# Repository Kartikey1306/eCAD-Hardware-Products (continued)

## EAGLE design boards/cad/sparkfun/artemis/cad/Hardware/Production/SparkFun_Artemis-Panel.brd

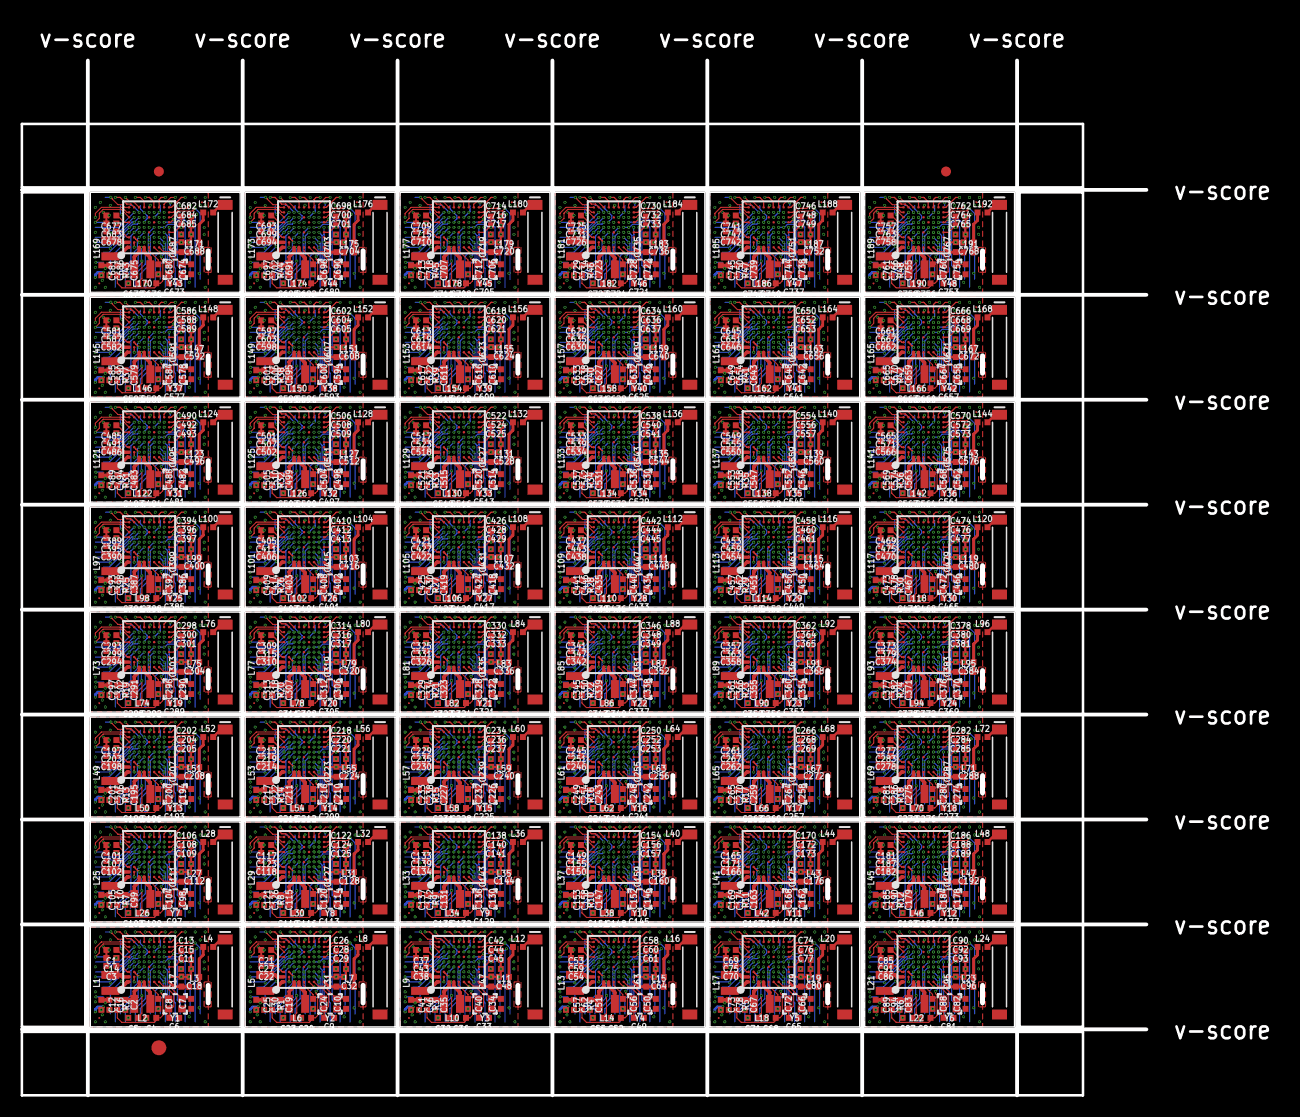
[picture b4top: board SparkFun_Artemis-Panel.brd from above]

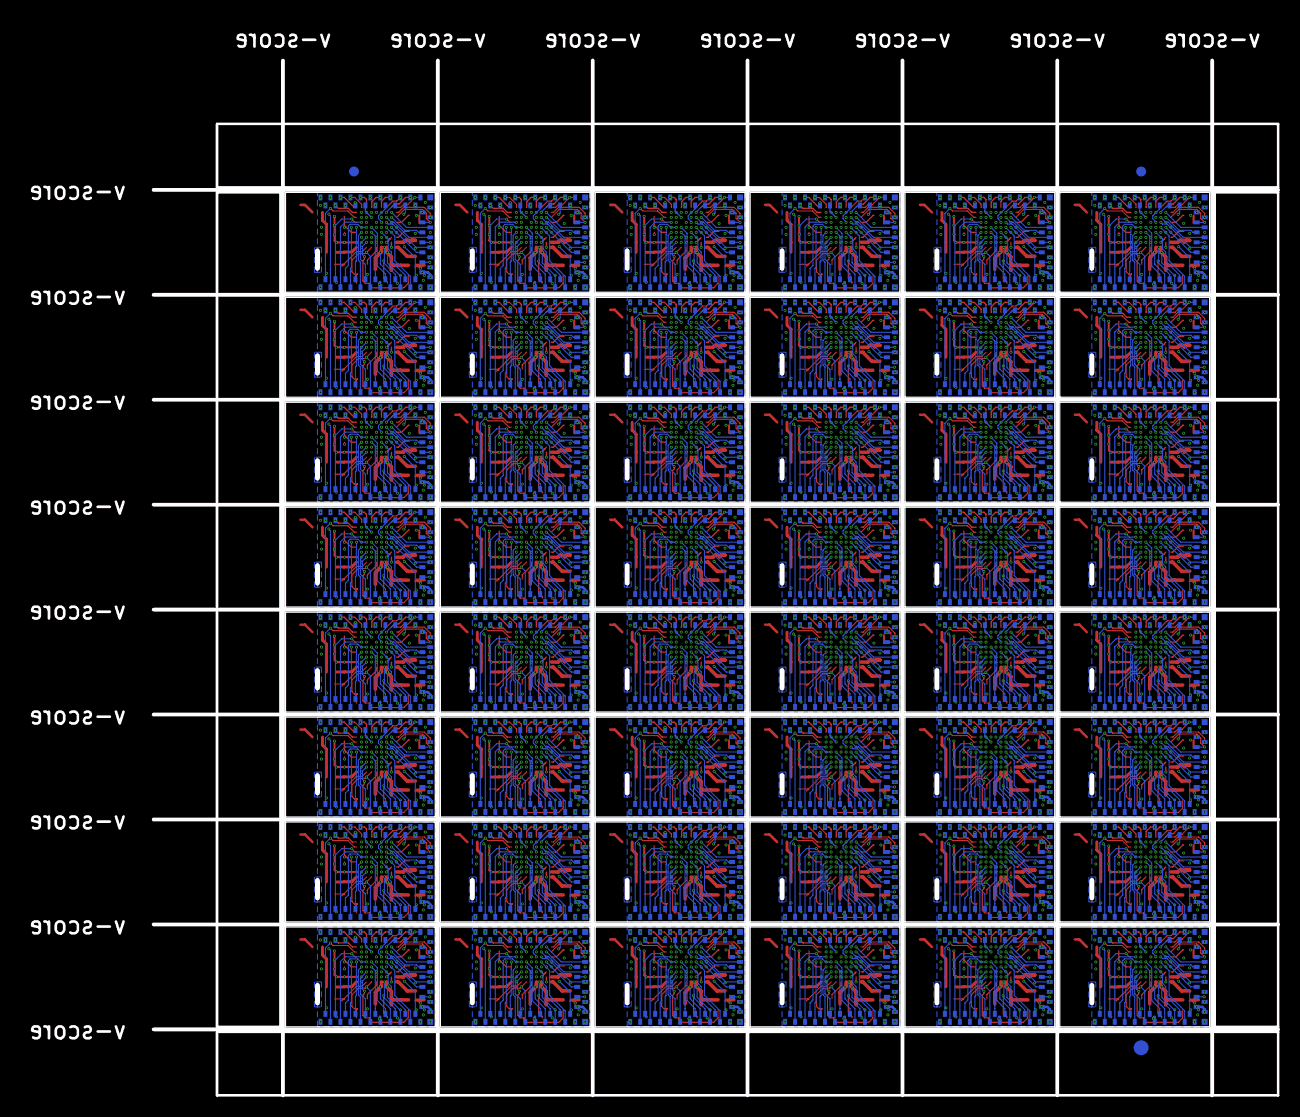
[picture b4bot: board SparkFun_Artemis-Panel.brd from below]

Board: 4 copper layers, 112.6 x 103.6 mm, 4134 parts (2835 on the bottom side), 3264 nets.

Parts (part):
A1, A2, A3, A4, A5, A6, A7, A8, A9, A10, A11, A12, A13, A14, A15, A16, A17, A18, A19, A20, A21, A22, A23, A24, A25, A26, A27, A28, A29, A30, A31, A32, A33, A34, A35, A36, A37, A38, A39, A40, A41, A42, A43, A44, A45, A46, A47, A48: 2.4GHZ-3.2X1.6MM; ANT-2.4GHZ-8.0X1.0MM
C1, C21, C37, C53, C69, C85, C101, C117, C133, C149, C165, C181, C197, C213, C229, C245, C261, C277, C293, C309, C325, C341, C357, C373, C389, C405, C421, C437, C453, C469, C485, C501, C517, C533, C549, C565, C581, C597, C613, C629, C645, C661, C677, C693, C709, C725, C741, C757: 0.47uF; 0402-TIGHT
C2, C19, C35, C51, C67, C83, C99, C115, C131, C147, C163, C179, C195, C211, C227, C243, C259, C275, C291, C307, C323, C339, C355, C371, C387, C403, C419, C435, C451, C467, C483, C499, C515, C531, C547, C563, C579, C595, C611, C627, C643, C659, C675, C691, C707, C723, C739, C755: 4.7uF; 0402-TIGHT
C3, C5, C8, C16, C22, C23, C24, C30, C38, C39, C40, C46, C54, C55, C56, C62, C70, C71, C72, C78, C86, C87, C88, C94, C102, C103, C104, C110, C118, C119, C120, C126, C134, C135, C136, C142, C150, C151, C152, C158, C166, C167, C168, C174, C182, C183, C184, C190, C198, C199, C200, C206, C214, C215, C216, C222, C230, C231, C232, C238, C246, C247, C248, C254, C262, C263, C264, C270, C278, C279, C280, C286, C294, C295, C296, C302, C310, C311, C312, C318, C326, C327, C328, C334, C342, C343, C344, C350, C358, C359, C360, C366, C374, C375, C376, C382, C390, C391, C392, C398, C406, C407, C408, C414, C422, C423, C424, C430, C438, C439, C440, C446, C454, C455, C456, C462, C470, C471, C472, C478, C486, C487, C488, C494, C502, C503, C504, C510, C518, C519, C520, C526, C534, C535, C536, C542, C550, C551, C552, C558, C566, C567, C568, C574, C582, C583, C584, C590, C598, C599, C600, C606, C614, C615, C616, C622, C630, C631, C632, C638, C646, C647, C648, C654, C662, C663, C664, C670, C678, C679, C680, C686, C694, C695, C696, C702, C710, C711, C712, C718, C726, C727, C728, C734, C742, C743, C744, C750, C758, C759, C760, C766: 2.2uF; 0402-TIGHT
C4, C12, C13, C14, C15, C20, C25, C26, C27, C28, C36, C41, C42, C43, C44, C52, C57, C58, C59, C60, C68, C73, C74, C75, C76, C84, C89, C90, C91, C92, C100, C105, C106, C107, C108, C116, C121, C122, C123, C124, C132, C137, C138, C139, C140, C148, C153, C154, C155, C156, C164, C169, C170, C171, C172, C180, C185, C186, C187, C188, C196, C201, C202, C203, C204, C212, C217, C218, C219, C220, C228, C233, C234, C235, C236, C244, C249, C250, C251, C252, C260, C265, C266, C267, C268, C276, C281, C282, C283, C284, C292, C297, C298, C299, C300, C308, C313, C314, C315, C316, C324, C329, C330, C331, C332, C340, C345, C346, C347, C348, C356, C361, C362, C363, C364, C372, C377, C378, C379, C380, C388, C393, C394, C395, C396, C404, C409, C410, C411, C412, C420, C425, C426, C427, C428, C436, C441, C442, C443, C444, C452, C457, C458, C459, C460, C468, C473, C474, C475, C476, C484, C489, C490, C491, C492, C500, C505, C506, C507, C508, C516, C521, C522, C523, C524, C532, C537, C538, C539, C540, C548, C553, C554, C555, C556, C564, C569, C570, C571, C572, C580, C585, C586, C587, C588, C596, C601, C602, C603, C604, C612, C617, C618, C619, C620, C628, C633, C634, C635, C636, C644, C649, C650, C651, C652, C660, C665, C666, C667, C668, C676, C681, C682, C683, C684, C692, C697, C698, C699, C700, C708, C713, C714, C715, C716, C724, C729, C730, C731, C732, C740, C745, C746, C747, C748, C756, C761, C762, C763, C764: 1.0uF; 0402-TIGHT
C6, C7, C9, C10, C33, C34, C49, C50, C65, C66, C81, C82, C97, C98, C113, C114, C129, C130, C145, C146, C161, C162, C177, C178, C193, C194, C209, C210, C225, C226, C241, C242, C257, C258, C273, C274, C289, C290, C305, C306, C321, C322, C337, C338, C353, C354, C369, C370, C385, C386, C401, C402, C417, C418, C433, C434, C449, C450, C465, C466, C481, C482, C497, C498, C513, C514, C529, C530, C545, C546, C561, C562, C577, C578, C593, C594, C609, C610, C625, C626, C641, C642, C657, C658, C673, C674, C689, C690, C705, C706, C721, C722, C737, C738, C753, C754: 6pF; 0402-TIGHT
C11, C29, C45, C61, C77, C93, C109, C125, C141, C157, C173, C189, C205, C221, C237, C253, C269, C285, C301, C317, C333, C349, C365, C381, C397, C413, C429, C445, C461, C477, C493, C509, C525, C541, C557, C573, C589, C605, C621, C637, C653, C669, C685, C701, C717, C733, C749, C765: 47nF; 0402-TIGHT
C17, C31, C47, C63, C79, C95, C111, C127, C143, C159, C175, C191, C207, C223, C239, C255, C271, C287, C303, C319, C335, C351, C367, C383, C399, C415, C431, C447, C463, C479, C495, C511, C527, C543, C559, C575, C591, C607, C623, C639, C655, C671, C687, C703, C719, C735, C751, C767: DNP; 0402-TIGHT
C18, C32, C48, C64, C80, C96, C112, C128, C144, C160, C176, C192, C208, C224, C240, C256, C272, C288, C304, C320, C336, C352, C368, C384, C400, C416, C432, C448, C464, C480, C496, C512, C528, C544, C560, C576, C592, C608, C624, C640, C656, C672, C688, C704, C720, C736, C752, C768: 0.5pF; 0402-TIGHT
E$1, E$2, E$3, E$4: FIDUCIAL-1X2
E$5, E$6: FIDUCIAL-1.5X3
FD1, FD2, FD3, FD4, FD5, FD6, FD7, FD8, FD9, FD10, FD11, FD12, FD13, FD14, FD15, FD16, FD17, FD18, FD19, FD20, FD21, FD22, FD23, FD24, FD25, FD26, FD27, FD28, FD29, FD30, FD31, FD32, FD33, FD34, FD35, FD36, FD37, FD38, FD39, FD40, FD41, FD42, FD43, FD44, FD45, FD46, FD47, FD48, FD49, FD50, FD51, FD52, FD53, FD54, FD55, FD56, FD57, FD58, FD59, FD60, FD61, FD62, FD63, FD64, FD65, FD66, FD67, FD68, FD69, FD70, FD71, FD72, FD73, FD74, FD75, FD76, FD77, FD78, FD79, FD80, FD81, FD82, FD83, FD84, FD85, FD86, FD87, FD88, FD89, FD90, FD91, FD92, FD93, FD94, FD95, FD96: FIDUCIAL0.2MM; FIDUCIAL-0.2MM
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
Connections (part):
!RST: J50.1, U1.G3
!RST1: J83.1, U2.G3
!RST2: J142.1, U3.G3
!RST3: J201.1, U4.G3
!RST4: J260.1, U5.G3
!RST5: J319.1, U6.G3
!RST6: J378.1, U7.G3
!RST7: J437.1, U8.G3
!RST8: J496.1, U9.G3
!RST9: J555.1, U10.G3
!RST10: J614.1, U11.G3
!RST11: J673.1, U12.G3
!RST12: J732.1, U13.G3
!RST13: J791.1, U14.G3
!RST14: J850.1, U15.G3
!RST15: J909.1, U16.G3
!RST16: J968.1, U17.G3
!RST17: J1027.1, U18.G3
!RST18: J1086.1, U19.G3
!RST19: J1145.1, U20.G3
!RST20: J1204.1, U21.G3
!RST21: J1263.1, U22.G3
!RST22: J1322.1, U23.G3
!RST23: J1381.1, U24.G3
!RST24: J1440.1, U25.G3
!RST25: J1499.1, U26.G3
!RST26: J1558.1, U27.G3
!RST27: J1617.1, U28.G3
!RST28: J1676.1, U29.G3
!RST29: J1735.1, U30.G3
!RST30: J1794.1, U31.G3
!RST31: J1853.1, U32.G3
!RST32: J1912.1, U33.G3
!RST33: J1971.1, U34.G3
!RST34: J2030.1, U35.G3
!RST35: J2089.1, U36.G3
!RST36: J2148.1, U37.G3
!RST37: J2207.1, U38.G3
!RST38: J2266.1, U39.G3
!RST39: J2325.1, U40.G3
!RST40: J2384.1, U41.G3
!RST41: J2443.1, U42.G3
!RST42: J2502.1, U43.G3
!RST43: J2561.1, U44.G3
!RST44: J2620.1, U45.G3
!RST45: J2679.1, U46.G3
!RST46: J2738.1, U47.G3
!RST47: J2797.1, U48.G3
ADC_VREF: C1.1, U1.A6
ADC_VREF1: C21.1, U2.A6
ADC_VREF2: C37.1, U3.A6
ADC_VREF3: C53.1, U4.A6
ADC_VREF4: C69.1, U5.A6
ADC_VREF5: C85.1, U6.A6
ADC_VREF6: C101.1, U7.A6
ADC_VREF7: C117.1, U8.A6
ADC_VREF8: C133.1, U9.A6
ADC_VREF9: C149.1, U10.A6
ADC_VREF10: C165.1, U11.A6
ADC_VREF11: C181.1, U12.A6
ADC_VREF12: C197.1, U13.A6
ADC_VREF13: C213.1, U14.A6
ADC_VREF14: C229.1, U15.A6
ADC_VREF15: C245.1, U16.A6
ADC_VREF16: C261.1, U17.A6
ADC_VREF17: C277.1, U18.A6
ADC_VREF18: C293.1, U19.A6
ADC_VREF19: C309.1, U20.A6
ADC_VREF20: C325.1, U21.A6
ADC_VREF21: C341.1, U22.A6
ADC_VREF22: C357.1, U23.A6
ADC_VREF23: C373.1, U24.A6
ADC_VREF24: C389.1, U25.A6
ADC_VREF25: C405.1, U26.A6
ADC_VREF26: C421.1, U27.A6
ADC_VREF27: C437.1, U28.A6
ADC_VREF28: C453.1, U29.A6
ADC_VREF29: C469.1, U30.A6
ADC_VREF30: C485.1, U31.A6
ADC_VREF31: C501.1, U32.A6
ADC_VREF32: C517.1, U33.A6
ADC_VREF33: C533.1, U34.A6
ADC_VREF34: C549.1, U35.A6
ADC_VREF35: C565.1, U36.A6
ADC_VREF36: C581.1, U37.A6
ADC_VREF37: C597.1, U38.A6
ADC_VREF38: C613.1, U39.A6
ADC_VREF39: C629.1, U40.A6
ADC_VREF40: C645.1, U41.A6
ADC_VREF41: C661.1, U42.A6
ADC_VREF42: C677.1, U43.A6
ADC_VREF43: C693.1, U44.A6
ADC_VREF44: C709.1, U45.A6
ADC_VREF45: C725.1, U46.A6
ADC_VREF46: C741.1, U47.A6
ADC_VREF47: C757.1, U48.A6
BOOTLOAD: J7.1, U1.H9
BOOTLOAD1: J62.1, U2.H9
BOOTLOAD2: J121.1, U3.H9
BOOTLOAD3: J180.1, U4.H9
BOOTLOAD4: J239.1, U5.H9
BOOTLOAD5: J298.1, U6.H9
BOOTLOAD6: J357.1, U7.H9
BOOTLOAD7: J416.1, U8.H9
BOOTLOAD8: J475.1, U9.H9
BOOTLOAD9: J534.1, U10.H9
BOOTLOAD10: J593.1, U11.H9
BOOTLOAD11: J652.1, U12.H9
BOOTLOAD12: J711.1, U13.H9
BOOTLOAD13: J770.1, U14.H9
BOOTLOAD14: J829.1, U15.H9
BOOTLOAD15: J888.1, U16.H9
BOOTLOAD16: J947.1, U17.H9
BOOTLOAD17: J1006.1, U18.H9
BOOTLOAD18: J1065.1, U19.H9
BOOTLOAD19: J1124.1, U20.H9
BOOTLOAD20: J1183.1, U21.H9
BOOTLOAD21: J1242.1, U22.H9
BOOTLOAD22: J1301.1, U23.H9
BOOTLOAD23: J1360.1, U24.H9
BOOTLOAD24: J1419.1, U25.H9
BOOTLOAD25: J1478.1, U26.H9
BOOTLOAD26: J1537.1, U27.H9
BOOTLOAD27: J1596.1, U28.H9
BOOTLOAD28: J1655.1, U29.H9
BOOTLOAD29: J1714.1, U30.H9
BOOTLOAD30: J1773.1, U31.H9
BOOTLOAD31: J1832.1, U32.H9
BOOTLOAD32: J1891.1, U33.H9
BOOTLOAD33: J1950.1, U34.H9
BOOTLOAD34: J2009.1, U35.H9
BOOTLOAD35: J2068.1, U36.H9
BOOTLOAD36: J2127.1, U37.H9
BOOTLOAD37: J2186.1, U38.H9
BOOTLOAD38: J2245.1, U39.H9
BOOTLOAD39: J2304.1, U40.H9
BOOTLOAD40: J2363.1, U41.H9
BOOTLOAD41: J2422.1, U42.H9
BOOTLOAD42: J2481.1, U43.H9
BOOTLOAD43: J2540.1, U44.H9
BOOTLOAD44: J2599.1, U45.H9
BOOTLOAD45: J2658.1, U46.H9
BOOTLOAD46: J2717.1, U47.H9
BOOTLOAD47: J2776.1, U48.H9
D0: J51.1, U1.H4
D1: J49.1, U1.G4
D2: J48.1, U1.F4
D3: J54.1, U1.G5
D4: J77.1, U2.F9
D5: J80.1, U2.J9
D6: J92.1, U2.J6
D7: J13.1, U1.F9
D8: J11.1, U1.F8
D9: J6.1, U1.G7
D10: J8.1, U1.G8
D11: J94.1, U2.H6
D12: J98.1, U2.F8
D13: J99.1, U2.G8
D14: J20.1, U1.D7
D15: J29.1, U1.C7
D16: J42.1, U1.D4
D17: J43.1, U1.D3
D18: J41.1, U1.C5
D19: J40.1, U1.C3
D20: J101.1, U2.G7
D21: J107.1, U2.G5
D22: J106.1, U2.F4
D23: J18.1, U1.D8
D24: J105.1, U2.G4
D25: J104.1, U2.H4
D26: J108.1, U2.D7
D27: J109.1, U2.C7
D28: J110.1, U2.D4
D29: J111.1, U2.D3
D30: J112.1, U2.C5
D31: J113.1, U2.C3
D32: J114.1, U2.D8
D33: J115.1, U2.C6
D34: J31.1, U1.C6
D35: J116.1, U2.E5
D36: J55.1, U1.H6
D37: J117.1, U2.F5
D38: J56.1, U1.J6
D39: J136.1, U3.F9
D40: J5.1, U1.J9
D41: J45.1, U1.E5
D42: J139.1, U3.J9
D43: J151.1, U3.J6
D44: J153.1, U3.H6
D45: J46.1, U1.F5
D46: J157.1, U3.F8
D47: J158.1, U3.G8
D48: J160.1, U3.G7
D49: J166.1, U3.G5
D50: J165.1, U3.F4
D51: J164.1, U3.G4
D52: J163.1, U3.H4
D53: J167.1, U3.D7
D54: J168.1, U3.C7
D55: J169.1, U3.D4
D56: J170.1, U3.D3
D57: J171.1, U3.C5
D58: J172.1, U3.C3
D59: J173.1, U3.D8
D60: J174.1, U3.C6
D61: J175.1, U3.E5
D62: J176.1, U3.F5
D63: J195.1, U4.F9
D64: J198.1, U4.J9
D65: J210.1, U4.J6
D66: J212.1, U4.H6
D67: J216.1, U4.F8
D68: J217.1, U4.G8
D69: J219.1, U4.G7
D70: J225.1, U4.G5
D71: J224.1, U4.F4
D72: J223.1, U4.G4
D73: J222.1, U4.H4
D74: J226.1, U4.D7
D75: J227.1, U4.C7
D76: J228.1, U4.D4
D77: J229.1, U4.D3
D78: J230.1, U4.C5
D79: J231.1, U4.C3
D80: J232.1, U4.D8
D81: J233.1, U4.C6
D82: J234.1, U4.E5
D83: J235.1, U4.F5
D84: J254.1, U5.F9
D85: J257.1, U5.J9
D86: J269.1, U5.J6
D87: J271.1, U5.H6
D88: J275.1, U5.F8
D89: J276.1, U5.G8
D90: J278.1, U5.G7
D91: J284.1, U5.G5
D92: J283.1, U5.F4
D93: J282.1, U5.G4
D94: J281.1, U5.H4
D95: J285.1, U5.D7
D96: J286.1, U5.C7
D97: J287.1, U5.D4
D98: J288.1, U5.D3
D99: J289.1, U5.C5
D100: J290.1, U5.C3
D101: J291.1, U5.D8
D102: J292.1, U5.C6
D103: J293.1, U5.E5
D104: J294.1, U5.F5
D105: J313.1, U6.F9
D106: J316.1, U6.J9
D107: J328.1, U6.J6
D108: J330.1, U6.H6
D109: J334.1, U6.F8
D110: J335.1, U6.G8
D111: J337.1, U6.G7
D112: J343.1, U6.G5
D113: J342.1, U6.F4
D114: J341.1, U6.G4
D115: J340.1, U6.H4
D116: J344.1, U6.D7
D117: J345.1, U6.C7
D118: J346.1, U6.D4
D119: J347.1, U6.D3
D120: J348.1, U6.C5
D121: J349.1, U6.C3
D122: J350.1, U6.D8
D123: J351.1, U6.C6
D124: J352.1, U6.E5
D125: J353.1, U6.F5
D126: J372.1, U7.F9
D127: J375.1, U7.J9
D128: J387.1, U7.J6
D129: J389.1, U7.H6
D130: J393.1, U7.F8
D131: J394.1, U7.G8
D132: J396.1, U7.G7
D133: J402.1, U7.G5
D134: J401.1, U7.F4
D135: J400.1, U7.G4
D136: J399.1, U7.H4
D137: J403.1, U7.D7
D138: J404.1, U7.C7
D139: J405.1, U7.D4
D140: J406.1, U7.D3
D141: J407.1, U7.C5
D142: J408.1, U7.C3
D143: J409.1, U7.D8
D144: J410.1, U7.C6
D145: J411.1, U7.E5
D146: J412.1, U7.F5
D147: J431.1, U8.F9
D148: J434.1, U8.J9
D149: J446.1, U8.J6
D150: J448.1, U8.H6
D151: J452.1, U8.F8
D152: J453.1, U8.G8
D153: J455.1, U8.G7
D154: J461.1, U8.G5
D155: J460.1, U8.F4
D156: J459.1, U8.G4
D157: J458.1, U8.H4
D158: J462.1, U8.D7
D159: J463.1, U8.C7
D160: J464.1, U8.D4
D161: J465.1, U8.D3
D162: J466.1, U8.C5
D163: J467.1, U8.C3
D164: J468.1, U8.D8
D165: J469.1, U8.C6
D166: J470.1, U8.E5
D167: J471.1, U8.F5
D168: J490.1, U9.F9
D169: J493.1, U9.J9
D170: J505.1, U9.J6
D171: J507.1, U9.H6
D172: J511.1, U9.F8
D173: J512.1, U9.G8
D174: J514.1, U9.G7
D175: J520.1, U9.G5
D176: J519.1, U9.F4
D177: J518.1, U9.G4
D178: J517.1, U9.H4
D179: J521.1, U9.D7
D180: J522.1, U9.C7
D181: J523.1, U9.D4
D182: J524.1, U9.D3
D183: J525.1, U9.C5
D184: J526.1, U9.C3
D185: J527.1, U9.D8
D186: J528.1, U9.C6
D187: J529.1, U9.E5
D188: J530.1, U9.F5
D189: J549.1, U10.F9
D190: J552.1, U10.J9
D191: J564.1, U10.J6
D192: J566.1, U10.H6
D193: J570.1, U10.F8
D194: J571.1, U10.G8
D195: J573.1, U10.G7
D196: J579.1, U10.G5
D197: J578.1, U10.F4
D198: J577.1, U10.G4
D199: J576.1, U10.H4
D200: J580.1, U10.D7
D201: J581.1, U10.C7
D202: J582.1, U10.D4
D203: J583.1, U10.D3
D204: J584.1, U10.C5
D205: J585.1, U10.C3
D206: J586.1, U10.D8
D207: J587.1, U10.C6
D208: J588.1, U10.E5
D209: J589.1, U10.F5
D210: J608.1, U11.F9
D211: J611.1, U11.J9
D212: J623.1, U11.J6
D213: J625.1, U11.H6
D214: J629.1, U11.F8
D215: J630.1, U11.G8
D216: J632.1, U11.G7
D217: J638.1, U11.G5
D218: J637.1, U11.F4
D219: J636.1, U11.G4
D220: J635.1, U11.H4
D221: J639.1, U11.D7
D222: J640.1, U11.C7
D223: J641.1, U11.D4
D224: J642.1, U11.D3
D225: J643.1, U11.C5
D226: J644.1, U11.C3
D227: J645.1, U11.D8
D228: J646.1, U11.C6
D229: J647.1, U11.E5
D230: J648.1, U11.F5
D231: J667.1, U12.F9
D232: J670.1, U12.J9
D233: J682.1, U12.J6
D234: J684.1, U12.H6
D235: J688.1, U12.F8
D236: J689.1, U12.G8
D237: J691.1, U12.G7
D238: J697.1, U12.G5
D239: J696.1, U12.F4
D240: J695.1, U12.G4
D241: J694.1, U12.H4
D242: J698.1, U12.D7
D243: J699.1, U12.C7
D244: J700.1, U12.D4
D245: J701.1, U12.D3
D246: J702.1, U12.C5
D247: J703.1, U12.C3
D248: J704.1, U12.D8
D249: J705.1, U12.C6
D250: J706.1, U12.E5
D251: J707.1, U12.F5
D252: J726.1, U13.F9
D253: J729.1, U13.J9
D254: J741.1, U13.J6
D255: J743.1, U13.H6
D256: J747.1, U13.F8
D257: J748.1, U13.G8
D258: J750.1, U13.G7
D259: J756.1, U13.G5
D260: J755.1, U13.F4
D261: J754.1, U13.G4
D262: J753.1, U13.H4
D263: J757.1, U13.D7
D264: J758.1, U13.C7
D265: J759.1, U13.D4
D266: J760.1, U13.D3
D267: J761.1, U13.C5
D268: J762.1, U13.C3
D269: J763.1, U13.D8
D270: J764.1, U13.C6
D271: J765.1, U13.E5
D272: J766.1, U13.F5
D273: J785.1, U14.F9
D274: J788.1, U14.J9
D275: J800.1, U14.J6
D276: J802.1, U14.H6
D277: J806.1, U14.F8
D278: J807.1, U14.G8
D279: J809.1, U14.G7
D280: J815.1, U14.G5
D281: J814.1, U14.F4
D282: J813.1, U14.G4
D283: J812.1, U14.H4
D284: J816.1, U14.D7
D285: J817.1, U14.C7
D286: J818.1, U14.D4
D287: J819.1, U14.D3
D288: J820.1, U14.C5
D289: J821.1, U14.C3
D290: J822.1, U14.D8
D291: J823.1, U14.C6
D292: J824.1, U14.E5
D293: J825.1, U14.F5
D294: J844.1, U15.F9
D295: J847.1, U15.J9
D296: J859.1, U15.J6
D297: J861.1, U15.H6
D298: J865.1, U15.F8
D299: J866.1, U15.G8
D300: J868.1, U15.G7
D301: J874.1, U15.G5
D302: J873.1, U15.F4
D303: J872.1, U15.G4
D304: J871.1, U15.H4
D305: J875.1, U15.D7
D306: J876.1, U15.C7
D307: J877.1, U15.D4
D308: J878.1, U15.D3
D309: J879.1, U15.C5
D310: J880.1, U15.C3
D311: J881.1, U15.D8
D312: J882.1, U15.C6
D313: J883.1, U15.E5
D314: J884.1, U15.F5
D315: J903.1, U16.F9
D316: J906.1, U16.J9
D317: J918.1, U16.J6
D318: J920.1, U16.H6
D319: J924.1, U16.F8
D320: J925.1, U16.G8
D321: J927.1, U16.G7
D322: J933.1, U16.G5
D323: J932.1, U16.F4
D324: J931.1, U16.G4
D325: J930.1, U16.H4
D326: J934.1, U16.D7
D327: J935.1, U16.C7
D328: J936.1, U16.D4
D329: J937.1, U16.D3
D330: J938.1, U16.C5
D331: J939.1, U16.C3
D332: J940.1, U16.D8
D333: J941.1, U16.C6
D334: J942.1, U16.E5
D335: J943.1, U16.F5
D336: J962.1, U17.F9
D337: J965.1, U17.J9
D338: J977.1, U17.J6
D339: J979.1, U17.H6
D340: J983.1, U17.F8
D341: J984.1, U17.G8
D342: J986.1, U17.G7
D343: J992.1, U17.G5
D344: J991.1, U17.F4
D345: J990.1, U17.G4
D346: J989.1, U17.H4
D347: J993.1, U17.D7
D348: J994.1, U17.C7
D349: J995.1, U17.D4
D350: J996.1, U17.D3
D351: J997.1, U17.C5
D352: J998.1, U17.C3
D353: J999.1, U17.D8
D354: J1000.1, U17.C6
D355: J1001.1, U17.E5
D356: J1002.1, U17.F5
D357: J1021.1, U18.F9
D358: J1024.1, U18.J9
D359: J1036.1, U18.J6
D360: J1038.1, U18.H6
D361: J1042.1, U18.F8
D362: J1043.1, U18.G8
D363: J1045.1, U18.G7
D364: J1051.1, U18.G5
D365: J1050.1, U18.F4
D366: J1049.1, U18.G4
D367: J1048.1, U18.H4
D368: J1052.1, U18.D7
D369: J1053.1, U18.C7
D370: J1054.1, U18.D4
D371: J1055.1, U18.D3
D372: J1056.1, U18.C5
D373: J1057.1, U18.C3
D374: J1058.1, U18.D8
D375: J1059.1, U18.C6
D376: J1060.1, U18.E5
D377: J1061.1, U18.F5
D378: J1080.1, U19.F9
D379: J1083.1, U19.J9
D380: J1095.1, U19.J6
D381: J1097.1, U19.H6
D382: J1101.1, U19.F8
D383: J1102.1, U19.G8
D384: J1104.1, U19.G7
D385: J1110.1, U19.G5
D386: J1109.1, U19.F4
D387: J1108.1, U19.G4
D388: J1107.1, U19.H4
D389: J1111.1, U19.D7
D390: J1112.1, U19.C7
D391: J1113.1, U19.D4
D392: J1114.1, U19.D3
D393: J1115.1, U19.C5
D394: J1116.1, U19.C3
D395: J1117.1, U19.D8
D396: J1118.1, U19.C6
D397: J1119.1, U19.E5
D398: J1120.1, U19.F5
D399: J1139.1, U20.F9
D400: J1142.1, U20.J9
D401: J1154.1, U20.J6
D402: J1156.1, U20.H6
D403: J1160.1, U20.F8
D404: J1161.1, U20.G8
D405: J1163.1, U20.G7
D406: J1169.1, U20.G5
D407: J1168.1, U20.F4
D408: J1167.1, U20.G4
D409: J1166.1, U20.H4
D410: J1170.1, U20.D7
D411: J1171.1, U20.C7
D412: J1172.1, U20.D4
D413: J1173.1, U20.D3
D414: J1174.1, U20.C5
D415: J1175.1, U20.C3
D416: J1176.1, U20.D8
D417: J1177.1, U20.C6
D418: J1178.1, U20.E5
D419: J1179.1, U20.F5
D420: J1198.1, U21.F9
D421: J1201.1, U21.J9
D422: J1213.1, U21.J6
D423: J1215.1, U21.H6
D424: J1219.1, U21.F8
D425: J1220.1, U21.G8
D426: J1222.1, U21.G7
D427: J1228.1, U21.G5
D428: J1227.1, U21.F4
D429: J1226.1, U21.G4
D430: J1225.1, U21.H4
D431: J1229.1, U21.D7
D432: J1230.1, U21.C7
D433: J1231.1, U21.D4
D434: J1232.1, U21.D3
D435: J1233.1, U21.C5
D436: J1234.1, U21.C3
D437: J1235.1, U21.D8
D438: J1236.1, U21.C6
D439: J1237.1, U21.E5
D440: J1238.1, U21.F5
D441: J1257.1, U22.F9
D442: J1260.1, U22.J9
D443: J1272.1, U22.J6
D444: J1274.1, U22.H6
D445: J1278.1, U22.F8
D446: J1279.1, U22.G8
D447: J1281.1, U22.G7
D448: J1287.1, U22.G5
D449: J1286.1, U22.F4
D450: J1285.1, U22.G4
D451: J1284.1, U22.H4
D452: J1288.1, U22.D7
D453: J1289.1, U22.C7
D454: J1290.1, U22.D4
D455: J1291.1, U22.D3
D456: J1292.1, U22.C5
D457: J1293.1, U22.C3
D458: J1294.1, U22.D8
D459: J1295.1, U22.C6
D460: J1296.1, U22.E5
D461: J1297.1, U22.F5
D462: J1316.1, U23.F9
D463: J1319.1, U23.J9
D464: J1331.1, U23.J6
D465: J1333.1, U23.H6
D466: J1337.1, U23.F8
D467: J1338.1, U23.G8
D468: J1340.1, U23.G7
D469: J1346.1, U23.G5
D470: J1345.1, U23.F4
D471: J1344.1, U23.G4
D472: J1343.1, U23.H4
D473: J1347.1, U23.D7
D474: J1348.1, U23.C7
D475: J1349.1, U23.D4
D476: J1350.1, U23.D3
D477: J1351.1, U23.C5
D478: J1352.1, U23.C3
D479: J1353.1, U23.D8
D480: J1354.1, U23.C6
D481: J1355.1, U23.E5
D482: J1356.1, U23.F5
D483: J1375.1, U24.F9
D484: J1378.1, U24.J9
D485: J1390.1, U24.J6
D486: J1392.1, U24.H6
D487: J1396.1, U24.F8
D488: J1397.1, U24.G8
D489: J1399.1, U24.G7
D490: J1405.1, U24.G5
D491: J1404.1, U24.F4
D492: J1403.1, U24.G4
D493: J1402.1, U24.H4
D494: J1406.1, U24.D7
D495: J1407.1, U24.C7
D496: J1408.1, U24.D4
D497: J1409.1, U24.D3
D498: J1410.1, U24.C5
D499: J1411.1, U24.C3
D500: J1412.1, U24.D8
D501: J1413.1, U24.C6
D502: J1414.1, U24.E5
D503: J1415.1, U24.F5
D504: J1434.1, U25.F9
D505: J1437.1, U25.J9
D506: J1449.1, U25.J6
D507: J1451.1, U25.H6
D508: J1455.1, U25.F8
D509: J1456.1, U25.G8
D510: J1458.1, U25.G7
D511: J1464.1, U25.G5
D512: J1463.1, U25.F4
D513: J1462.1, U25.G4
D514: J1461.1, U25.H4
D515: J1465.1, U25.D7
D516: J1466.1, U25.C7
D517: J1467.1, U25.D4
D518: J1468.1, U25.D3
D519: J1469.1, U25.C5
D520: J1470.1, U25.C3
D521: J1471.1, U25.D8
D522: J1472.1, U25.C6
D523: J1473.1, U25.E5
D524: J1474.1, U25.F5
D525: J1493.1, U26.F9
D526: J1496.1, U26.J9
D527: J1508.1, U26.J6
D528: J1510.1, U26.H6
D529: J1514.1, U26.F8
D530: J1515.1, U26.G8
D531: J1517.1, U26.G7
D532: J1523.1, U26.G5
D533: J1522.1, U26.F4
D534: J1521.1, U26.G4
D535: J1520.1, U26.H4
D536: J1524.1, U26.D7
D537: J1525.1, U26.C7
D538: J1526.1, U26.D4
D539: J1527.1, U26.D3
D540: J1528.1, U26.C5
D541: J1529.1, U26.C3
D542: J1530.1, U26.D8
D543: J1531.1, U26.C6
D544: J1532.1, U26.E5
D545: J1533.1, U26.F5
D546: J1552.1, U27.F9
D547: J1555.1, U27.J9
D548: J1567.1, U27.J6
D549: J1569.1, U27.H6
D550: J1573.1, U27.F8
D551: J1574.1, U27.G8
D552: J1576.1, U27.G7
D553: J1582.1, U27.G5
D554: J1581.1, U27.F4
D555: J1580.1, U27.G4
D556: J1579.1, U27.H4
D557: J1583.1, U27.D7
D558: J1584.1, U27.C7
D559: J1585.1, U27.D4
D560: J1586.1, U27.D3
D561: J1587.1, U27.C5
D562: J1588.1, U27.C3
D563: J1589.1, U27.D8
D564: J1590.1, U27.C6
D565: J1591.1, U27.E5
D566: J1592.1, U27.F5
D567: J1611.1, U28.F9
D568: J1614.1, U28.J9
D569: J1626.1, U28.J6
D570: J1628.1, U28.H6
D571: J1632.1, U28.F8
D572: J1633.1, U28.G8
D573: J1635.1, U28.G7
D574: J1641.1, U28.G5
D575: J1640.1, U28.F4
D576: J1639.1, U28.G4
D577: J1638.1, U28.H4
D578: J1642.1, U28.D7
D579: J1643.1, U28.C7
D580: J1644.1, U28.D4
D581: J1645.1, U28.D3
D582: J1646.1, U28.C5
D583: J1647.1, U28.C3
D584: J1648.1, U28.D8
D585: J1649.1, U28.C6
D586: J1650.1, U28.E5
D587: J1651.1, U28.F5
D588: J1670.1, U29.F9
D589: J1673.1, U29.J9
D590: J1685.1, U29.J6
D591: J1687.1, U29.H6
D592: J1691.1, U29.F8
D593: J1692.1, U29.G8
D594: J1694.1, U29.G7
D595: J1700.1, U29.G5
D596: J1699.1, U29.F4
D597: J1698.1, U29.G4
D598: J1697.1, U29.H4
D599: J1701.1, U29.D7
D600: J1702.1, U29.C7
D601: J1703.1, U29.D4
D602: J1704.1, U29.D3
D603: J1705.1, U29.C5
D604: J1706.1, U29.C3
D605: J1707.1, U29.D8
D606: J1708.1, U29.C6
D607: J1709.1, U29.E5
D608: J1710.1, U29.F5
D609: J1729.1, U30.F9
D610: J1732.1, U30.J9
D611: J1744.1, U30.J6
D612: J1746.1, U30.H6
D613: J1750.1, U30.F8
D614: J1751.1, U30.G8
D615: J1753.1, U30.G7
D616: J1759.1, U30.G5
D617: J1758.1, U30.F4
D618: J1757.1, U30.G4
D619: J1756.1, U30.H4
D620: J1760.1, U30.D7
D621: J1761.1, U30.C7
D622: J1762.1, U30.D4
D623: J1763.1, U30.D3
D624: J1764.1, U30.C5
D625: J1765.1, U30.C3
D626: J1766.1, U30.D8
D627: J1767.1, U30.C6
D628: J1768.1, U30.E5
D629: J1769.1, U30.F5
D630: J1788.1, U31.F9
D631: J1791.1, U31.J9
D632: J1803.1, U31.J6
D633: J1805.1, U31.H6
D634: J1809.1, U31.F8
D635: J1810.1, U31.G8
D636: J1812.1, U31.G7
D637: J1818.1, U31.G5
D638: J1817.1, U31.F4
D639: J1816.1, U31.G4
D640: J1815.1, U31.H4
D641: J1819.1, U31.D7
D642: J1820.1, U31.C7
D643: J1821.1, U31.D4
D644: J1822.1, U31.D3
D645: J1823.1, U31.C5
D646: J1824.1, U31.C3
D647: J1825.1, U31.D8
D648: J1826.1, U31.C6
D649: J1827.1, U31.E5
D650: J1828.1, U31.F5
D651: J1847.1, U32.F9
D652: J1850.1, U32.J9
D653: J1862.1, U32.J6
D654: J1864.1, U32.H6
D655: J1868.1, U32.F8
D656: J1869.1, U32.G8
D657: J1871.1, U32.G7
D658: J1877.1, U32.G5
D659: J1876.1, U32.F4
D660: J1875.1, U32.G4
D661: J1874.1, U32.H4
D662: J1878.1, U32.D7
D663: J1879.1, U32.C7
D664: J1880.1, U32.D4
D665: J1881.1, U32.D3
D666: J1882.1, U32.C5
D667: J1883.1, U32.C3
D668: J1884.1, U32.D8
D669: J1885.1, U32.C6
D670: J1886.1, U32.E5
D671: J1887.1, U32.F5
D672: J1906.1, U33.F9
D673: J1909.1, U33.J9
D674: J1921.1, U33.J6
D675: J1923.1, U33.H6
D676: J1927.1, U33.F8
D677: J1928.1, U33.G8
D678: J1930.1, U33.G7
D679: J1936.1, U33.G5
D680: J1935.1, U33.F4
D681: J1934.1, U33.G4
D682: J1933.1, U33.H4
D683: J1937.1, U33.D7
D684: J1938.1, U33.C7
D685: J1939.1, U33.D4
D686: J1940.1, U33.D3
D687: J1941.1, U33.C5
D688: J1942.1, U33.C3
D689: J1943.1, U33.D8
D690: J1944.1, U33.C6
D691: J1945.1, U33.E5
D692: J1946.1, U33.F5
D693: J1965.1, U34.F9
D694: J1968.1, U34.J9
D695: J1980.1, U34.J6
D696: J1982.1, U34.H6
D697: J1986.1, U34.F8
D698: J1987.1, U34.G8
D699: J1989.1, U34.G7
D700: J1995.1, U34.G5
D701: J1994.1, U34.F4
D702: J1993.1, U34.G4
D703: J1992.1, U34.H4
D704: J1996.1, U34.D7
D705: J1997.1, U34.C7
D706: J1998.1, U34.D4
D707: J1999.1, U34.D3
D708: J2000.1, U34.C5
D709: J2001.1, U34.C3
D710: J2002.1, U34.D8
D711: J2003.1, U34.C6
D712: J2004.1, U34.E5
D713: J2005.1, U34.F5
D714: J2024.1, U35.F9
D715: J2027.1, U35.J9
D716: J2039.1, U35.J6
D717: J2041.1, U35.H6
D718: J2045.1, U35.F8
D719: J2046.1, U35.G8
D720: J2048.1, U35.G7
D721: J2054.1, U35.G5
D722: J2053.1, U35.F4
D723: J2052.1, U35.G4
D724: J2051.1, U35.H4
D725: J2055.1, U35.D7
D726: J2056.1, U35.C7
D727: J2057.1, U35.D4
D728: J2058.1, U35.D3
D729: J2059.1, U35.C5
D730: J2060.1, U35.C3
D731: J2061.1, U35.D8
D732: J2062.1, U35.C6
D733: J2063.1, U35.E5
D734: J2064.1, U35.F5
D735: J2083.1, U36.F9
D736: J2086.1, U36.J9
D737: J2098.1, U36.J6
D738: J2100.1, U36.H6
D739: J2104.1, U36.F8
D740: J2105.1, U36.G8
D741: J2107.1, U36.G7
D742: J2113.1, U36.G5
D743: J2112.1, U36.F4
D744: J2111.1, U36.G4
D745: J2110.1, U36.H4
D746: J2114.1, U36.D7
D747: J2115.1, U36.C7
D748: J2116.1, U36.D4
D749: J2117.1, U36.D3
D750: J2118.1, U36.C5
D751: J2119.1, U36.C3
D752: J2120.1, U36.D8
D753: J2121.1, U36.C6
D754: J2122.1, U36.E5
D755: J2123.1, U36.F5
D756: J2142.1, U37.F9
D757: J2145.1, U37.J9
D758: J2157.1, U37.J6
D759: J2159.1, U37.H6
D760: J2163.1, U37.F8
D761: J2164.1, U37.G8
D762: J2166.1, U37.G7
D763: J2172.1, U37.G5
D764: J2171.1, U37.F4
D765: J2170.1, U37.G4
D766: J2169.1, U37.H4
D767: J2173.1, U37.D7
D768: J2174.1, U37.C7
D769: J2175.1, U37.D4
D770: J2176.1, U37.D3
D771: J2177.1, U37.C5
D772: J2178.1, U37.C3
D773: J2179.1, U37.D8
D774: J2180.1, U37.C6
D775: J2181.1, U37.E5
D776: J2182.1, U37.F5
D777: J2201.1, U38.F9
D778: J2204.1, U38.J9
D779: J2216.1, U38.J6
D780: J2218.1, U38.H6
D781: J2222.1, U38.F8
D782: J2223.1, U38.G8
D783: J2225.1, U38.G7
D784: J2231.1, U38.G5
D785: J2230.1, U38.F4
D786: J2229.1, U38.G4
D787: J2228.1, U38.H4
D788: J2232.1, U38.D7
D789: J2233.1, U38.C7
D790: J2234.1, U38.D4
D791: J2235.1, U38.D3
D792: J2236.1, U38.C5
D793: J2237.1, U38.C3
D794: J2238.1, U38.D8
D795: J2239.1, U38.C6
D796: J2240.1, U38.E5
D797: J2241.1, U38.F5
D798: J2260.1, U39.F9
D799: J2263.1, U39.J9
D800: J2275.1, U39.J6
D801: J2277.1, U39.H6
D802: J2281.1, U39.F8
D803: J2282.1, U39.G8
D804: J2284.1, U39.G7
D805: J2290.1, U39.G5
D806: J2289.1, U39.F4
D807: J2288.1, U39.G4
D808: J2287.1, U39.H4
D809: J2291.1, U39.D7
D810: J2292.1, U39.C7
D811: J2293.1, U39.D4
D812: J2294.1, U39.D3
D813: J2295.1, U39.C5
D814: J2296.1, U39.C3
D815: J2297.1, U39.D8
D816: J2298.1, U39.C6
D817: J2299.1, U39.E5
D818: J2300.1, U39.F5
D819: J2319.1, U40.F9
D820: J2322.1, U40.J9
D821: J2334.1, U40.J6
D822: J2336.1, U40.H6
D823: J2340.1, U40.F8
D824: J2341.1, U40.G8
D825: J2343.1, U40.G7
D826: J2349.1, U40.G5
D827: J2348.1, U40.F4
D828: J2347.1, U40.G4
D829: J2346.1, U40.H4
D830: J2350.1, U40.D7
D831: J2351.1, U40.C7
D832: J2352.1, U40.D4
D833: J2353.1, U40.D3
D834: J2354.1, U40.C5
D835: J2355.1, U40.C3
D836: J2356.1, U40.D8
D837: J2357.1, U40.C6
D838: J2358.1, U40.E5
D839: J2359.1, U40.F5
D840: J2378.1, U41.F9
D841: J2381.1, U41.J9
D842: J2393.1, U41.J6
D843: J2395.1, U41.H6
D844: J2399.1, U41.F8
D845: J2400.1, U41.G8
D846: J2402.1, U41.G7
D847: J2408.1, U41.G5
D848: J2407.1, U41.F4
D849: J2406.1, U41.G4
D850: J2405.1, U41.H4
D851: J2409.1, U41.D7
D852: J2410.1, U41.C7
D853: J2411.1, U41.D4
D854: J2412.1, U41.D3
D855: J2413.1, U41.C5
D856: J2414.1, U41.C3
D857: J2415.1, U41.D8
D858: J2416.1, U41.C6
D859: J2417.1, U41.E5
D860: J2418.1, U41.F5
D861: J2437.1, U42.F9
D862: J2440.1, U42.J9
D863: J2452.1, U42.J6
D864: J2454.1, U42.H6
D865: J2458.1, U42.F8
D866: J2459.1, U42.G8
D867: J2461.1, U42.G7
D868: J2467.1, U42.G5
D869: J2466.1, U42.F4
D870: J2465.1, U42.G4
D871: J2464.1, U42.H4
D872: J2468.1, U42.D7
D873: J2469.1, U42.C7
D874: J2470.1, U42.D4
D875: J2471.1, U42.D3
D876: J2472.1, U42.C5
D877: J2473.1, U42.C3
D878: J2474.1, U42.D8
D879: J2475.1, U42.C6
D880: J2476.1, U42.E5
D881: J2477.1, U42.F5
D882: J2496.1, U43.F9
D883: J2499.1, U43.J9
D884: J2511.1, U43.J6
D885: J2513.1, U43.H6
D886: J2517.1, U43.F8
D887: J2518.1, U43.G8
D888: J2520.1, U43.G7
D889: J2526.1, U43.G5
D890: J2525.1, U43.F4
D891: J2524.1, U43.G4
D892: J2523.1, U43.H4
D893: J2527.1, U43.D7
D894: J2528.1, U43.C7
D895: J2529.1, U43.D4
D896: J2530.1, U43.D3
D897: J2531.1, U43.C5
D898: J2532.1, U43.C3
D899: J2533.1, U43.D8
D900: J2534.1, U43.C6
D901: J2535.1, U43.E5
D902: J2536.1, U43.F5
D903: J2555.1, U44.F9
D904: J2558.1, U44.J9
D905: J2570.1, U44.J6
D906: J2572.1, U44.H6
D907: J2576.1, U44.F8
D908: J2577.1, U44.G8
D909: J2579.1, U44.G7
D910: J2585.1, U44.G5
D911: J2584.1, U44.F4
D912: J2583.1, U44.G4
D913: J2582.1, U44.H4
D914: J2586.1, U44.D7
D915: J2587.1, U44.C7
D916: J2588.1, U44.D4
D917: J2589.1, U44.D3
D918: J2590.1, U44.C5
D919: J2591.1, U44.C3
D920: J2592.1, U44.D8
D921: J2593.1, U44.C6
D922: J2594.1, U44.E5
D923: J2595.1, U44.F5
D924: J2614.1, U45.F9
D925: J2617.1, U45.J9
D926: J2629.1, U45.J6
D927: J2631.1, U45.H6
D928: J2635.1, U45.F8
D929: J2636.1, U45.G8
D930: J2638.1, U45.G7
D931: J2644.1, U45.G5
D932: J2643.1, U45.F4
D933: J2642.1, U45.G4
D934: J2641.1, U45.H4
D935: J2645.1, U45.D7
D936: J2646.1, U45.C7
D937: J2647.1, U45.D4
D938: J2648.1, U45.D3
D939: J2649.1, U45.C5
D940: J2650.1, U45.C3
D941: J2651.1, U45.D8
D942: J2652.1, U45.C6
D943: J2653.1, U45.E5
D944: J2654.1, U45.F5
D945: J2673.1, U46.F9
D946: J2676.1, U46.J9
D947: J2688.1, U46.J6
D948: J2690.1, U46.H6
D949: J2694.1, U46.F8
D950: J2695.1, U46.G8
D951: J2697.1, U46.G7
D952: J2703.1, U46.G5
D953: J2702.1, U46.F4
D954: J2701.1, U46.G4
D955: J2700.1, U46.H4
D956: J2704.1, U46.D7
D957: J2705.1, U46.C7
D958: J2706.1, U46.D4
D959: J2707.1, U46.D3
D960: J2708.1, U46.C5
D961: J2709.1, U46.C3
D962: J2710.1, U46.D8
D963: J2711.1, U46.C6
D964: J2712.1, U46.E5
D965: J2713.1, U46.F5
D966: J2732.1, U47.F9
D967: J2735.1, U47.J9
D968: J2747.1, U47.J6
D969: J2749.1, U47.H6
D970: J2753.1, U47.F8
D971: J2754.1, U47.G8
D972: J2756.1, U47.G7
D973: J2762.1, U47.G5
D974: J2761.1, U47.F4
D975: J2760.1, U47.G4
D976: J2759.1, U47.H4
D977: J2763.1, U47.D7
D978: J2764.1, U47.C7
D979: J2765.1, U47.D4
D980: J2766.1, U47.D3
D981: J2767.1, U47.C5
D982: J2768.1, U47.C3
D983: J2769.1, U47.D8
D984: J2770.1, U47.C6
D985: J2771.1, U47.E5
D986: J2772.1, U47.F5
D987: J2791.1, U48.F9
D988: J2794.1, U48.J9
D989: J2806.1, U48.J6
D990: J2808.1, U48.H6
D991: J2812.1, U48.F8
D992: J2813.1, U48.G8
D993: J2815.1, U48.G7
D994: J2821.1, U48.G5
D995: J2820.1, U48.F4
D996: J2819.1, U48.G4
D997: J2818.1, U48.H4
D998: J2822.1, U48.D7
D999: J2823.1, U48.C7
D1000: J2824.1, U48.D4
D1001: J2825.1, U48.D3
D1002: J2826.1, U48.C5
D1003: J2827.1, U48.C3
D1004: J2828.1, U48.D8
D1005: J2829.1, U48.C6
D1006: J2830.1, U48.E5
D1007: J2831.1, U48.F5
DVDD: C11.1, U1.H3
DVDD1: C29.1, U2.H3
DVDD2: C45.1, U3.H3
DVDD3: C61.1, U4.H3
DVDD4: C77.1, U5.H3
DVDD5: C93.1, U6.H3
DVDD6: C109.1, U7.H3
DVDD7: C125.1, U8.H3
DVDD8: C141.1, U9.H3
DVDD9: C157.1, U10.H3
DVDD10: C173.1, U11.H3
DVDD11: C189.1, U12.H3
DVDD12: C205.1, U13.H3
DVDD13: C221.1, U14.H3
DVDD14: C237.1, U15.H3
DVDD15: C253.1, U16.H3
DVDD16: C269.1, U17.H3
DVDD17: C285.1, U18.H3
DVDD18: C301.1, U19.H3
DVDD19: C317.1, U20.H3
DVDD20: C333.1, U21.H3
DVDD21: C349.1, U22.H3
DVDD22: C365.1, U23.H3
DVDD23: C381.1, U24.H3
DVDD24: C397.1, U25.H3
DVDD25: C413.1, U26.H3
DVDD26: C429.1, U27.H3
DVDD27: C445.1, U28.H3
DVDD28: C461.1, U29.H3
DVDD29: C477.1, U30.H3
DVDD30: C493.1, U31.H3
DVDD31: C509.1, U32.H3
DVDD32: C525.1, U33.H3
DVDD33: C541.1, U34.H3
DVDD34: C557.1, U35.H3
DVDD35: C573.1, U36.H3
DVDD36: C589.1, U37.H3
DVDD37: C605.1, U38.H3
DVDD38: C621.1, U39.H3
DVDD39: C637.1, U40.H3
DVDD40: C653.1, U41.H3
DVDD41: C669.1, U42.H3
DVDD42: C685.1, U43.H3
DVDD43: C701.1, U44.H3
DVDD44: C717.1, U45.H3
DVDD45: C733.1, U46.H3
DVDD46: C749.1, U47.H3
DVDD47: C765.1, U48.H3
GND: C1.2, C2.2, C3.2, C4.2, C5.2, C6.1, C7.1, C8.2, C11.2, C12.2, C13.2, C14.2, C15.2, C16.2, C17.2, C18.2, J1.1, J22.1, J38.1, J39.1, J47.1, J59.1, U1.B3, U1.C2, U1.E2, U1.E3, U1.F2, U1.H1, U1.H2, U1.J2
GND1: C9.1, C10.1, C19.2, C20.2, C21.2, C22.2, C23.2, C24.2, C25.2, C26.2, C27.2, C28.2, C29.2, C30.2, C31.2, C32.2, J88.1, J89.1, J90.1, J100.1, J102.1, J118.1, U2.B3, U2.C2, U2.E2, U2.E3, U2.F2, U2.H1, U2.H2, U2.J2
GND2: C33.1, C34.1, C35.2, C36.2, C37.2, C38.2, C39.2, C40.2, C41.2, C42.2, C43.2, C44.2, C45.2, C46.2, C47.2, C48.2, J147.1, J148.1, J149.1, J159.1, J161.1, J177.1, U3.B3, U3.C2, U3.E2, U3.E3, U3.F2, U3.H1, U3.H2, U3.J2
GND3: C49.1, C50.1, C51.2, C52.2, C53.2, C54.2, C55.2, C56.2, C57.2, C58.2, C59.2, C60.2, C61.2, C62.2, C63.2, C64.2, J206.1, J207.1, J208.1, J218.1, J220.1, J236.1, U4.B3, U4.C2, U4.E2, U4.E3, U4.F2, U4.H1, U4.H2, U4.J2
GND4: C65.1, C66.1, C67.2, C68.2, C69.2, C70.2, C71.2, C72.2, C73.2, C74.2, C75.2, C76.2, C77.2, C78.2, C79.2, C80.2, J265.1, J266.1, J267.1, J277.1, J279.1, J295.1, U5.B3, U5.C2, U5.E2, U5.E3, U5.F2, U5.H1, U5.H2, U5.J2
GND5: C81.1, C82.1, C83.2, C84.2, C85.2, C86.2, C87.2, C88.2, C89.2, C90.2, C91.2, C92.2, C93.2, C94.2, C95.2, C96.2, J324.1, J325.1, J326.1, J336.1, J338.1, J354.1, U6.B3, U6.C2, U6.E2, U6.E3, U6.F2, U6.H1, U6.H2, U6.J2
GND6: C97.1, C98.1, C99.2, C100.2, C101.2, C102.2, C103.2, C104.2, C105.2, C106.2, C107.2, C108.2, C109.2, C110.2, C111.2, C112.2, J383.1, J384.1, J385.1, J395.1, J397.1, J413.1, U7.B3, U7.C2, U7.E2, U7.E3, U7.F2, U7.H1, U7.H2, U7.J2
GND7: C113.1, C114.1, C115.2, C116.2, C117.2, C118.2, C119.2, C120.2, C121.2, C122.2, C123.2, C124.2, C125.2, C126.2, C127.2, C128.2, J442.1, J443.1, J444.1, J454.1, J456.1, J472.1, U8.B3, U8.C2, U8.E2, U8.E3, U8.F2, U8.H1, U8.H2, U8.J2
GND8: C129.1, C130.1, C131.2, C132.2, C133.2, C134.2, C135.2, C136.2, C137.2, C138.2, C139.2, C140.2, C141.2, C142.2, C143.2, C144.2, J501.1, J502.1, J503.1, J513.1, J515.1, J531.1, U9.B3, U9.C2, U9.E2, U9.E3, U9.F2, U9.H1, U9.H2, U9.J2
GND9: C145.1, C146.1, C147.2, C148.2, C149.2, C150.2, C151.2, C152.2, C153.2, C154.2, C155.2, C156.2, C157.2, C158.2, C159.2, C160.2, J560.1, J561.1, J562.1, J572.1, J574.1, J590.1, U10.B3, U10.C2, U10.E2, U10.E3, U10.F2, U10.H1, U10.H2, U10.J2
GND10: C161.1, C162.1, C163.2, C164.2, C165.2, C166.2, C167.2, C168.2, C169.2, C170.2, C171.2, C172.2, C173.2, C174.2, C175.2, C176.2, J619.1, J620.1, J621.1, J631.1, J633.1, J649.1, U11.B3, U11.C2, U11.E2, U11.E3, U11.F2, U11.H1, U11.H2, U11.J2
GND11: C177.1, C178.1, C179.2, C180.2, C181.2, C182.2, C183.2, C184.2, C185.2, C186.2, C187.2, C188.2, C189.2, C190.2, C191.2, C192.2, J678.1, J679.1, J680.1, J690.1, J692.1, J708.1, U12.B3, U12.C2, U12.E2, U12.E3, U12.F2, U12.H1, U12.H2, U12.J2
GND12: C193.1, C194.1, C195.2, C196.2, C197.2, C198.2, C199.2, C200.2, C201.2, C202.2, C203.2, C204.2, C205.2, C206.2, C207.2, C208.2, J737.1, J738.1, J739.1, J749.1, J751.1, J767.1, U13.B3, U13.C2, U13.E2, U13.E3, U13.F2, U13.H1, U13.H2, U13.J2
GND13: C209.1, C210.1, C211.2, C212.2, C213.2, C214.2, C215.2, C216.2, C217.2, C218.2, C219.2, C220.2, C221.2, C222.2, C223.2, C224.2, J796.1, J797.1, J798.1, J808.1, J810.1, J826.1, U14.B3, U14.C2, U14.E2, U14.E3, U14.F2, U14.H1, U14.H2, U14.J2
GND14: C225.1, C226.1, C227.2, C228.2, C229.2, C230.2, C231.2, C232.2, C233.2, C234.2, C235.2, C236.2, C237.2, C238.2, C239.2, C240.2, J855.1, J856.1, J857.1, J867.1, J869.1, J885.1, U15.B3, U15.C2, U15.E2, U15.E3, U15.F2, U15.H1, U15.H2, U15.J2
GND15: C241.1, C242.1, C243.2, C244.2, C245.2, C246.2, C247.2, C248.2, C249.2, C250.2, C251.2, C252.2, C253.2, C254.2, C255.2, C256.2, J914.1, J915.1, J916.1, J926.1, J928.1, J944.1, U16.B3, U16.C2, U16.E2, U16.E3, U16.F2, U16.H1, U16.H2, U16.J2
GND16: C257.1, C258.1, C259.2, C260.2, C261.2, C262.2, C263.2, C264.2, C265.2, C266.2, C267.2, C268.2, C269.2, C270.2, C271.2, C272.2, J973.1, J974.1, J975.1, J985.1, J987.1, J1003.1, U17.B3, U17.C2, U17.E2, U17.E3, U17.F2, U17.H1, U17.H2, U17.J2
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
